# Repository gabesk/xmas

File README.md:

# xmas
# xmascard
Merry Christmas!

Welcome to the Electronic Christmas Tree Christmas Card. As you no doubt figured out already, to get started just push the button and enjoy the light show.

Additionally, this board is intended to be at least somewhat more than just an amusement; you can do things with it, and the entire schematic and program are open source on GitHub for you to see.

It’s powered by a Lattice FPGA, and you can add new patterns by plugging the USB connector in to the computer.

Unfortunately, I haven't gotten a chance to document this yet; I'll try to do so by Christmas itself. In the meantime, you can poke at the source code and try the instructions below, but I'm not sure they are actually correct. :(

## Interacting with the board

Double click the `light_control.py` file on your computer. It should open a window. Click **Connect**, and follow the instructions. It will ask you to plug in the Christmas Tree board, and if all goes well, it will print that it was successfully connected in the bottom of the window.

Now that you're connected, click any of the lights on the tree. They should change on the board, too! :)

## Creating your own patterns
What else can you do? Well, you can make your own patterns, using the `convert_animation_file.py` and `upload_new_pattern.py` programs.

These programs accept text files containing animations patterns and downloads them to the board for display.

The animation files work like so:

Each step in the animation is specified on a line. Each line specifies the brightness of the LEDs, from the top left to the bottom right. Each LED is two digits from 0 to 7 for the red, then green brightness. The value 0 is off, while 7 is all the way bright. For readability, spaces can be added as desired and are ignored.

For example, to light the red LED on the top, then the entire row of green on the bottom, the line would look like the following:

```
70  00  00 00  00 00 00  07 07 07 07  00
```

Since that can still be hard to read, you can alternately put the LEDs on different lines and separate each step in the animation with a blank line.

This allows you to write the pattern out visually. For example, the above example could also be written as:

```
            70
            00
          00  00
        00  00  00
      07  07  07  07
            00
```

The animation runs at a fixed speed of # frames per second, and the board stores 256 animation steps for a total of # seconds of animation. If you don't use all 256 frames of animation, the program will just repeat the last frame until memory is full.

In order to make it a little easier to create animations, you can tell the program to fade between animation steps automatically.
For example, to create an animation which fades between all the LEDs on, off again, then back on, create a text file like so:

```
set_marker
       77
       77
     77  77
   77  77  77
 77  77  77  77
       77
       77
fade_to
       00
       00
     00  00
   00  00  00
 00  00  00  00
       00
fade_to
       77
       77
     77  77
   77  77  77
 77  77  77  77
       77
       77
repeat_forever
```

Suppose your text file is named animation.txt. First, convert it to an FPGA memory entry like so:
```
convert_animation_file.py animation.txt memory.txt
```
Next, program it to the FPGA like so:
```
upload_new_pattern.py COM3 memory.txt
```
You can find the correct value to use for COM3 by running the `light_control.py` and looking at the value in the box at the bottom of the program after clicking **Connect**.
If everything went well, you should see your animation running on the FPGA. If not, well, you can either treat this as an exercise in learning about Python, or email me and I'll help. :)

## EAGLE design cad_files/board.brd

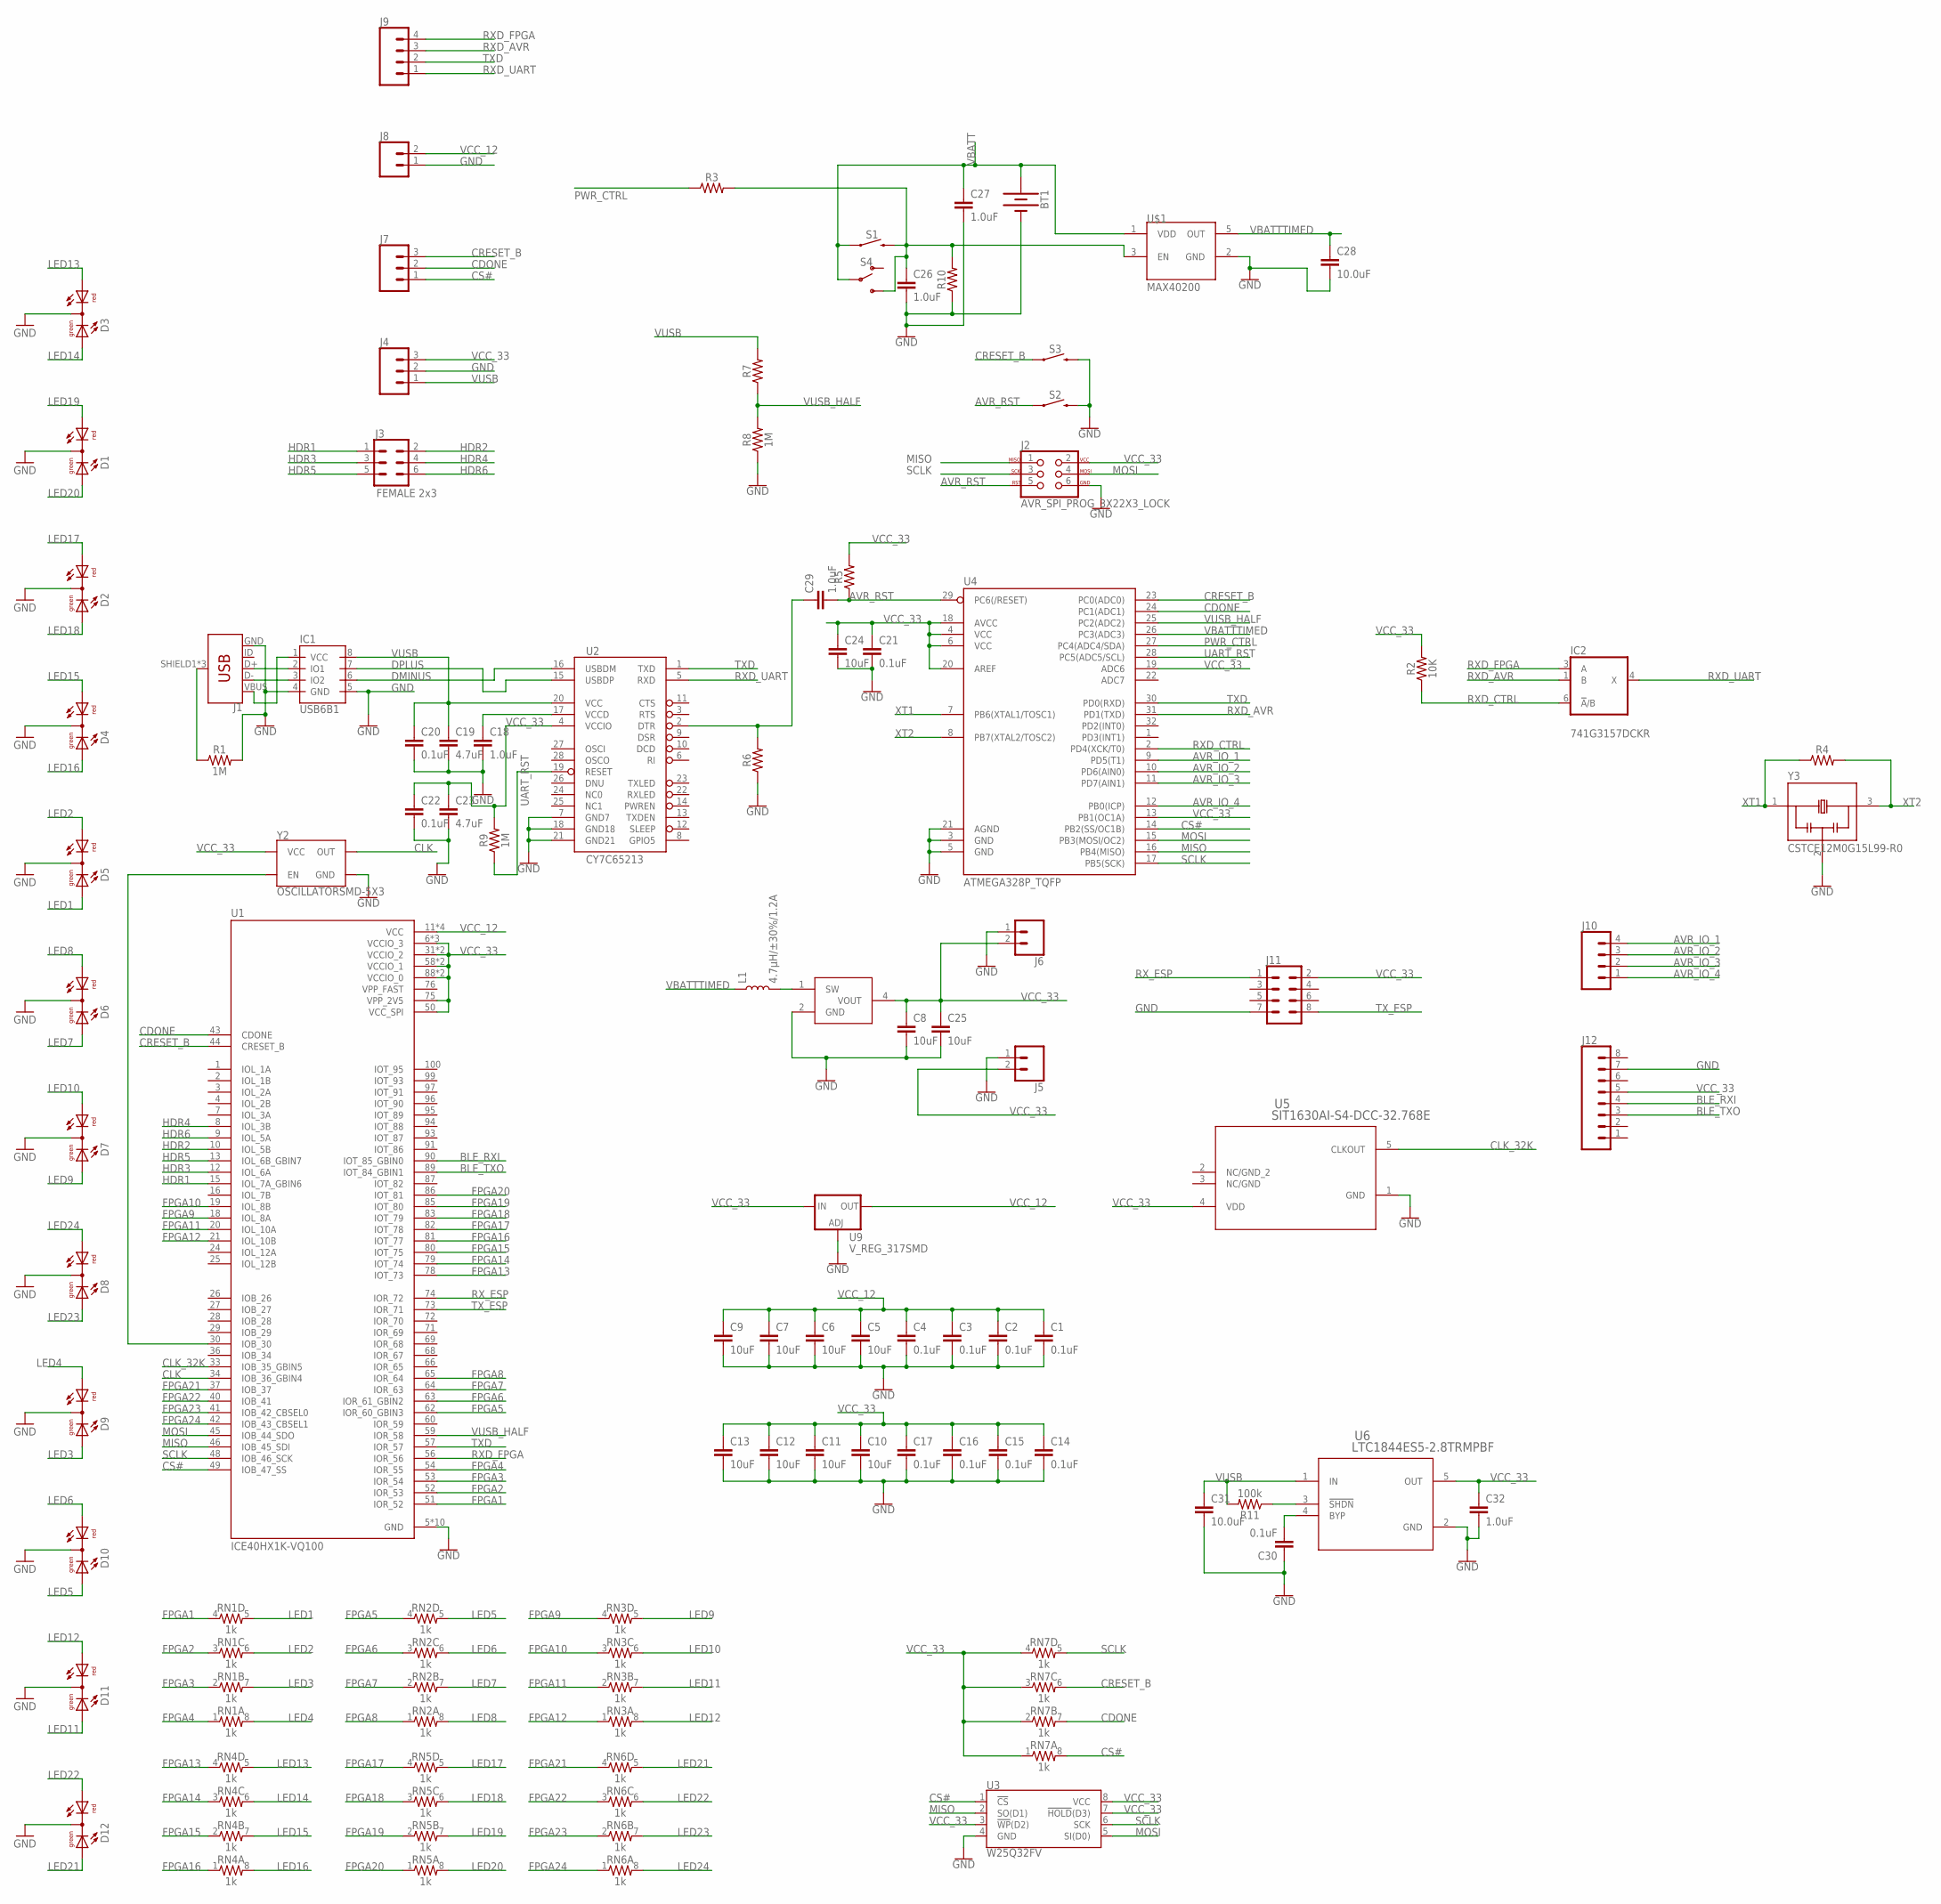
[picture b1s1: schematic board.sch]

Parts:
BT1: BATTERY-20MM_SMD; BATTCON_20MM
C1, C2, C3, C4, C14, C15, C16, C17, C20, C21, C22, C30: 0.1uF; 0805
C5, C6, C7, C8, C9, C10, C11, C12, C13, C24, C25: 10uF; 0805
C18, C29, C32: 1.0uF; 0805
C19, C23: 4.7uF; 0805
C26, C27: 1.0uF; 0603
C28: 10.0uF; 0603
C31: 10.0uF; 0805
D1, D2, D3, D4, D5, D6, D7, D8, D9, D10, D11, D12: DUOLED5MM
IC1: USB6B1; SO08
IC2: 741G3157DCKR; DCK_R-PDSO-G6
J1: USB_MICRO-B_FEMALE-SMT; USB-B-MICRO-SMD
J2: AVR_SPI_PROG_3X22X3_LOCK; 2X3_LOCK
J3: FEMALE 2x3; 2X3
J4, J7: CONN_03LOCK; 1X03_LOCK
J5, J6, J8: CONN_02LOCK; 1X02_LOCK
J9, J10: CONN_04LOCK; 1X04_LOCK
J11: CONN_04X2; 2X4
J12: CONN_08LOCK; 1X08_LOCK
L1: 4.7µH/±30%/1.2A; INDUCTOR_4.7UH
R1, R8, R9: 1M; 0805
R2: 10K; 0805
R3, R4, R5, R6, R7, R10: 0805
R11: 100k; 0805
RN1, RN2, RN3, RN4, RN5, RN6, RN7: 1k; 0805-ARV
S1, S2, S3: MOMENTARY-SWITCH-SPST-SMD-5.2MM; TACTILE_SWITCH_SMD_5.2MM
S4: SWITCH-SPDT-PTH-11.6X4.0MM; SWITCH_SPDT_PTH_11.6X4.0MM
U1: ICE40HX1K-VQ100; QFP50P1600X1600X120-100N
U2: CY7C65213; SSOP28DB
U3: W25Q32FV; SOIC-8
U4: ATMEGA328P_TQFP; TQFP32-08
U5: SIT1630AI-S4-DCC-32.768E; SOT_SIT1630-S_SIT
U6: LTC1844ES5-2.8TRMPBF; S_5_ADI
U9: V_REG_317SMD; SOT223
U$1: MAX40200; SOT95P280X145-5N
U$2: TPS613221A; SOT95P280X145-5N
Y2: OSCILLATORSMD-5X3; OSCILLATOR-SMD-5X3.2
Y3: CSTCE12M0G15L99-R0; OSC_CSTCE12M0G15L99-R0

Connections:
AVR_IO_1: J10.4, U4.9 (PD5(T1))
AVR_IO_2: J10.3, U4.10 (PD6(AIN0))
AVR_IO_3: J10.2, U4.11 (PD7(AIN1))
AVR_IO_4: J10.1, U4.12 (PB0(ICP))
AVR_RST: C29.2, J2.5, R5.1, S2.1, U4.29 (PC6(/RESET))
BLE_RXI: J12.4, U1.90 (IOT_85_GBIN0)
BLE_TXO: J12.3, U1.89 (IOT_84_GBIN1)
CDONE: J7.2, RN7.7 (2), U1.43 (CDONE), U4.24 (PC1(ADC1))
CLK: U1.34 (IOB_36_GBIN4), Y2.3 (OUT)
CLK_32K: U1.33 (IOB_35_GBIN5), U5.5 (CLKOUT)
CLK_EN: U1.30 (IOB_30), Y2.1 (EN)
CRESET_B: J7.3, RN7.6 (2), S3.1, U1.44 (CRESET_B), U4.23 (PC0(ADC0))
CS#: J7.1, RN7.8 (2), U1.49 (IOB_47_SS), U3.1 (!CS!), U4.14 (PB2(SS/OC1B))
DMINUS: IC1.6 (IO2), U2.16 (USBDM)
DPLUS: IC1.7 (IO1), U2.15 (USBDP)
FPGA1: RN1.4 (1), U1.51 (IOR_52)
FPGA2: RN1.3 (1), U1.52 (IOR_53)
FPGA3: RN1.2 (1), U1.53 (IOR_54)
FPGA4: RN1.1, U1.54 (IOR_55)
FPGA5: RN2.4 (1), U1.62 (IOR_60_GBIN3)
FPGA6: RN2.3 (1), U1.63 (IOR_61_GBIN2)
FPGA7: RN2.2 (1), U1.64 (IOR_63)
FPGA8: RN2.1, U1.65 (IOR_64)
FPGA9: RN3.4 (1), U1.18 (IOL_8A)
FPGA10: RN3.3 (1), U1.19 (IOL_8B)
FPGA11: RN3.2 (1), U1.20 (IOL_10A)
FPGA12: RN3.1, U1.21 (IOL_10B)
FPGA13: RN4.4 (1), U1.78 (IOT_73)
FPGA14: RN4.3 (1), U1.79 (IOT_74)
FPGA15: RN4.2 (1), U1.80 (IOT_75)
FPGA16: RN4.1, U1.81 (IOT_77)
FPGA17: RN5.4 (1), U1.82 (IOT_78)
FPGA18: RN5.3 (1), U1.83 (IOT_79)
FPGA19: RN5.2 (1), U1.85 (IOT_80)
FPGA20: RN5.1, U1.86 (IOT_81)
FPGA21: RN6.4 (1), U1.37 (IOB_37)
FPGA22: RN6.3 (1), U1.40 (IOB_41)
FPGA23: RN6.2 (1), U1.41 (IOB_42_CBSEL0)
FPGA24: RN6.1, U1.42 (IOB_43_CBSEL1)
GND: BT1.2 (-), C1.2, C2.2, C3.2, C4.2, C5.2, C6.2, C7.2, C8.2, C9.2, C10.2, C11.2, C12.2, C13.2, C14.2, C15.2, C16.2, C17.2, C18.2, C19.2, C20.2, C21.2, C22.2, C23.2, C24.2, C25.2, C26.2, C27.2, C28.2, C30.1, C31.2, C32.2, D1.K (C), D2.K (C), D3.K (C), D4.K (C), D5.K (C), D6.K (C), D7.K (C), D8.K (C), D9.K (C), D10.K (C), D11.K (C), D12.K (C), IC1.4 (GND), IC1.5 (GND), IC2.2 (GND), J1.GND, J2.6, J4.2, J5.1, J6.1, J8.1, J11.7, J12.7, R1.2, R6.1, R8.1, R10.1, S2.3 (2), S3.3 (2), U1.5 (GND), U1.17 (GND), U1.23 (GND), U1.32 (GND), U1.39 (GND), U1.47 (GND), U1.55 (GND), U1.70 (GND), U1.84 (GND), U1.98 (GND), U2.7 (GND7), U2.18 (GND18), U2.21 (GND21), U3.4 (GND), U4.3 (GND), U4.5 (GND), U4.21 (AGND), U5.1 (GND), U6.2 (GND), U9.1 (ADJ), U$1.2 (GND), U$2.2 (GND), Y2.2 (GND), Y3.2
HDR1: J3.1, U1.15 (IOL_7A_GBIN6)
HDR2: J3.2, U1.10 (IOL_5B)
HDR3: J3.3, U1.12 (IOL_6A)
HDR4: J3.4, U1.8 (IOL_3B)
HDR5: J3.5, U1.13 (IOL_6B_GBIN7)
HDR6: J3.6, U1.9 (IOL_5A)
LED1: D5.AG, RN1.5 (2)
LED2: D5.AR, RN1.6 (2)
LED3: D9.AG, RN1.7 (2)
LED4: D9.AR, RN1.8 (2)
LED5: D10.AG, RN2.5 (2)
LED6: D10.AR, RN2.6 (2)
LED7: D6.AG, RN2.7 (2)
LED8: D6.AR, RN2.8 (2)
LED9: D7.AG, RN3.5 (2)
LED10: D7.AR, RN3.6 (2)
LED11: D11.AG, RN3.7 (2)
LED12: D11.AR, RN3.8 (2)
LED13: D3.AR, RN4.5 (2)
LED14: D3.AG, RN4.6 (2)
LED15: D4.AR, RN4.7 (2)
LED16: D4.AG, RN4.8 (2)
LED17: D2.AR, RN5.5 (2)
LED18: D2.AG, RN5.6 (2)
LED19: D1.AR, RN5.7 (2)
LED20: D1.AG, RN5.8 (2)
LED21: D12.AG, RN6.5 (2)
LED22: D12.AR, RN6.6 (2)
LED23: D8.AG, RN6.7 (2)
LED24: D8.AR, RN6.8 (2)
MISO: J2.1, U1.46 (IOB_45_SDI), U3.2 (SO(D1)), U4.16 (PB4(MISO))
MOSI: J2.4, U1.45 (IOB_44_SDO), U3.5 (SI(D0)), U4.15 (PB3(MOSI/OC2))
unnamed: C29.1, R6.2, U2.2 (DTR)
unnamed: C18.1, U2.17 (VCCD)
unnamed: J1.SHIELD1 (SHIELD), J1.SHIELD2 (SHIELD), J1.SHIELD3 (SHIELD), R1.1
unnamed: C26.1, R3.2, R10.2, S1.3 (2), S4.3 (S), U$1.3 (EN)
unnamed: C30.2, U6.4 (BYP)
unnamed: R11.1, U6.3 (!SHDN)
unnamed: IC1.2 (IO1), J1.D+
unnamed: IC1.3 (IO2), J1.D-
unnamed: L1.P$2 (2), U$2.1 (SW)
unnamed: IC1.1 (VCC), J1.VBUS
NC1: U2.25 (NC1)
PWR_CTRL: R3.1, U4.27 (PC4(ADC4/SDA))
RXD_AVR: IC2.1 (B), J9.3, U4.31 (PD1(TXD))
RXD_CTRL: IC2.6 (!A!/B), R2.1, U4.2 (PD4(XCK/T0))
RXD_FPGA: IC2.3 (A), J9.4, U1.56 (IOR_56)
RXD_UART: IC2.4 (X), J9.1, U2.5 (RXD)
RX_ESP: J11.1, U1.74 (IOR_72)
SCLK: J2.3, RN7.5 (2), U1.48 (IOB_46_SCK), U3.6 (SCK), U4.17 (PB5(SCK))
TXD: J9.2, U1.57 (IOR_57), U2.1 (TXD), U4.30 (PD0(RXD))
TX_ESP: J11.8, U1.73 (IOR_71)
UART_RST: R9.1, U2.19 (RESET), U4.28 (PC5(ADC5/SCL))
VBATT: BT1.1 (+), C27.1, S1.1, S4.2, U$1.1 (VDD)
VBATTTIMED: C28.1, L1.P$1 (1), U4.26 (PC3(ADC3)), U$1.5 (OUT)
VCC_12: C1.1, C2.1, C3.1, C4.1, C5.1, C6.1, C7.1, C9.1, J8.2, U1.11 (VCC), U1.35 (VCC), U1.61 (VCC), U1.77 (VCC), U9.2 (OUT)
VCC_33: C8.1, C10.1, C11.1, C12.1, C13.1, C14.1, C15.1, C16.1, C17.1, C21.1, C22.1, C23.1, C24.1, C25.1, C32.1, IC2.5 (VCC), J2.2, J4.3, J5.2, J6.2, J11.2, J12.5, R2.2, R5.2, R9.2, RN7.1, RN7.2 (1), RN7.3 (1), RN7.4 (1), U1.6 (VCCIO_3), U1.14 (VCCIO_3), U1.22 (VCCIO_3), U1.31 (VCCIO_2), U1.38 (VCCIO_2), U1.50 (VCC_SPI), U1.58 (VCCIO_1), U1.67 (VCCIO_1), U1.75 (VPP_2V5), U1.88 (VCCIO_0), U1.92 (VCCIO_0), U2.4 (VCCIO), U3.3 (!WP!(D2)), U3.7 (!HOLD!(D3)), U3.8 (VCC), U4.4 (VCC), U4.6 (VCC), U4.13 (PB1(OC1A)), U4.18 (AVCC), U4.19 (ADC6), U4.20 (AREF), U5.4 (VDD), U6.5 (OUT), U9.3 (IN), U$2.4 (VOUT), Y2.4 (VCC)
VPP_FAST: U1.76 (VPP_FAST)
VUSB: C19.1, C20.1, C31.1, IC1.8 (VCC), J4.1, R7.2, R11.2, U2.20 (VCC), U6.1 (IN)
VUSB_HALF: R7.1, R8.2, U1.59 (IOR_58), U4.25 (PC2(ADC2))
XT1: R4.1, U4.7 (PB6(XTAL1/TOSC1)), Y3.1
XT2: R4.2, U4.8 (PB7(XTAL2/TOSC2)), Y3.3

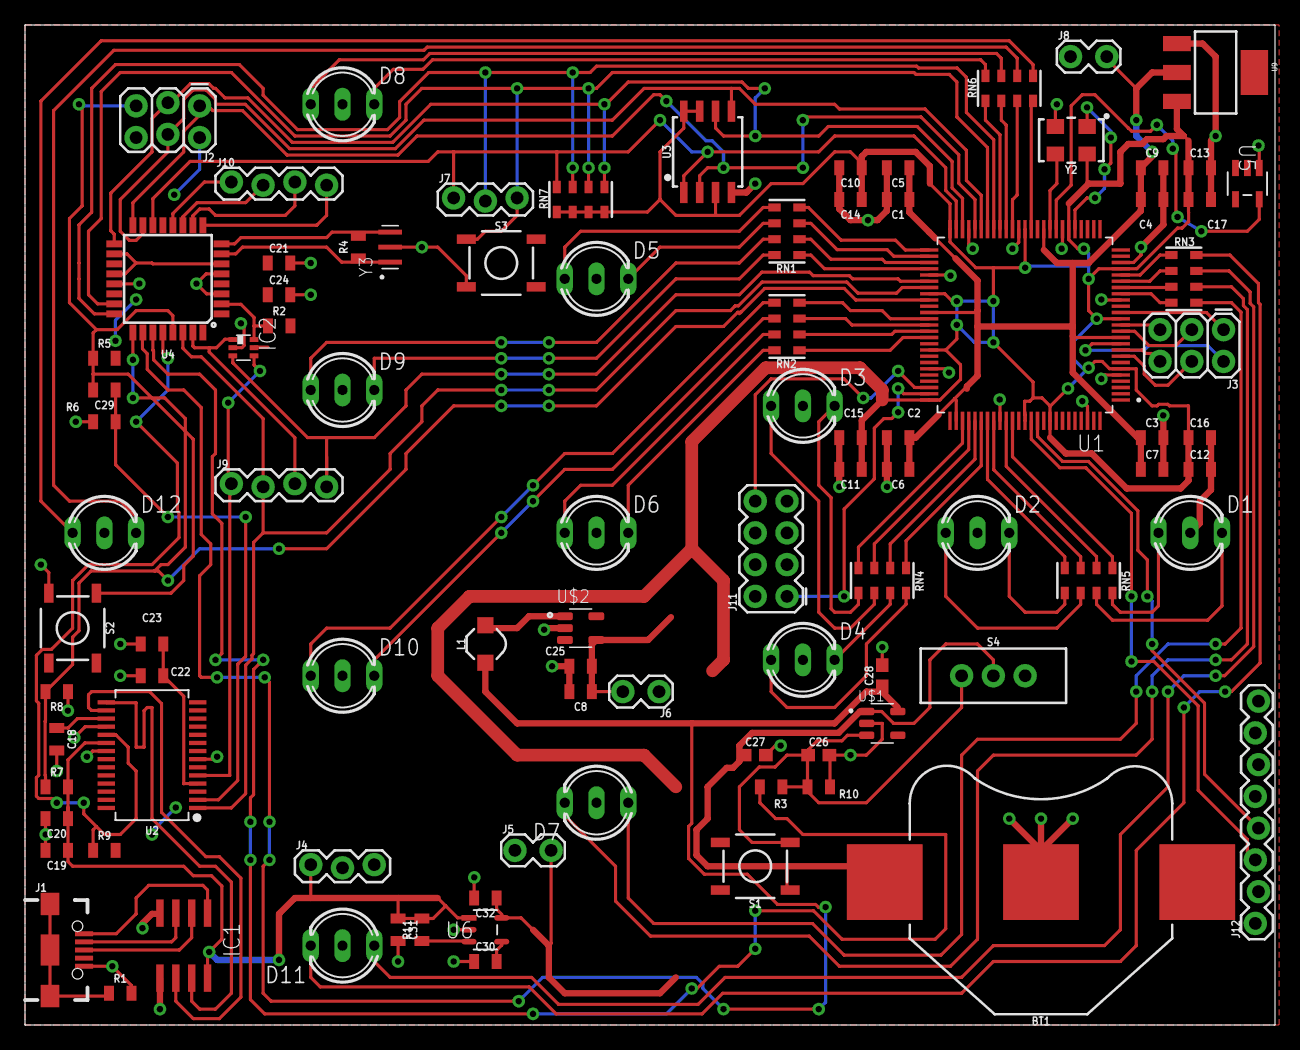
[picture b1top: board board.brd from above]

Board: 2 copper layers, 100.0 x 80.0 mm, 93 parts (0 on the bottom side), 100 nets.

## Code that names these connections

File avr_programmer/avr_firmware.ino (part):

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

#define PIN_CRESET PINC
#define PIN_CDONE PINC
#define PIN_VBATT PINC
#define PIN_UART_RST PINC
#define PIN_PWR_CTRL PINC
#define PIN_RXD_CTRL PIND


#define BIT_CRESET PINC0
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

void SetupFpgaResetAndDone() {
  // CRESET#  -> pin 23 -> PC0 (ADC0)
  // CDONE_B  -> pin 24 -> PC1 -> input (ADC1)
  // VBATT    -> pin 26 -> PC3 -> analog input (ADC3)
  // PWR_CTRL -> pin 27 -> PC4 -> output (ADC4)
  // RXD_CTRL -> pin 2  -> PD4 -> output
  //
  // Normally CRESET is open-circuit so it can float high
  // When we want to reset the FPGA, turn it to an input, low, so it pulls the FPGA low
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}

unsigned char ReadFpgaDoneBit() {
  if (PIN_CDONE & (1 << BIT_CDONE)) return 1;
  else return 0;
}

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
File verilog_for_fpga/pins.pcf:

# LED
set_io --warn-no-port leds[0] 85
set_io --warn-no-port leds[1] 86
set_io --warn-no-port leds[2] 82
set_io --warn-no-port leds[3] 83
set_io --warn-no-port leds[4] 78
set_io --warn-no-port leds[5] 79
set_io --warn-no-port leds[6] 80
set_io --warn-no-port leds[7] 81
set_io --warn-no-port leds[8] 52
set_io --warn-no-port leds[9] 51
set_io --warn-no-port leds[10] 65
set_io --warn-no-port leds[11] 64
set_io --warn-no-port leds[12] 18
set_io --warn-no-port leds[13] 19
set_io --warn-no-port leds[14] 42
set_io --warn-no-port leds[15] 41
set_io --warn-no-port leds[16] 54
set_io --warn-no-port leds[17] 53
set_io --warn-no-port leds[18] 63
set_io --warn-no-port leds[19] 62
set_io --warn-no-port leds[20] 20
set_io --warn-no-port leds[21] 21
set_io --warn-no-port leds[22] 40
set_io --warn-no-port leds[23] 37

set_io --warn-no-port clk_fast 34

#set_io --warn-no-port clk 13 # this one is the extra pin
#set_io --warn-no-port clk 45 # this is mosi or some shit when i was feeding it from the avr

set_io --warn-no-port clk_slow 33
set_io --warn-no-port clk_fast_en 30

set_io --warn-no-port vusb_half 59

set_io --warn-no-port rx 57
set_io --warn-no-port tx 56

set_io --warn-no-port user_io[0] 15
set_io --warn-no-port user_io[1] 10
set_io --warn-no-port user_io[2] 12
set_io --warn-no-port user_io[3] 8
set_io --warn-no-port user_io[4] 13
set_io --warn-no-port user_io[5] 9

set_io --warn-no-port ble_rxi 90
set_io --warn-no-port ble_txo 89

set_io --warn-no-port esp_rxi 74
set_io --warn-no-port esp_txo 73

set_io --warn-no-port cs_n 49
set_io --warn-no-port sclk 48
set_io --warn-no-port mosi 45
set_io --warn-no-port miso 46

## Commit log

2021-01-01 Update make_hdl.bat to accomodate refactoring of icestorm toolchain in apio utility
2021-05-26 Update for 115200 (instead of 38400) and make it parameterized for multiple baud rates.
2021-05-26 remove incorrect comment
2021-05-26 Update with comments on how it works
2021-05-26 Start flashing quicker (don't wait as long for bootloader to exit)
2021-05-26 Add demo application to change led colors from computer

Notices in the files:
parts and their libraries:
SparkFun-IC-Memory: Licensing: Creative Commons ShareAlike 4.0 International - https://creativecommons.org/licenses/by-sa/4.0
COPYRIGHT: Copyright (C) 2018 Accelerated Designs. All rights reserved
COPYRIGHT: Copyright (C) 2016 Accelerated Designs. All rights reserved
